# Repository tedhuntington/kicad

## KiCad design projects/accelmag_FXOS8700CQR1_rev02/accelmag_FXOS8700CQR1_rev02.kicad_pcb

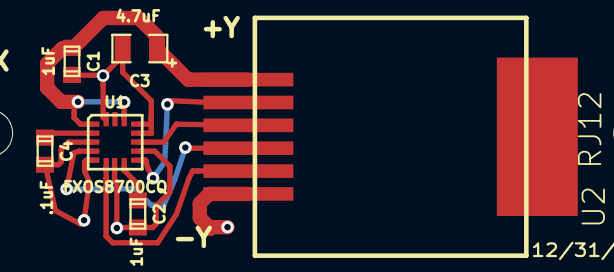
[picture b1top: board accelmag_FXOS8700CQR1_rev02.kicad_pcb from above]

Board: 2 copper layers, 8 parts (0 on the bottom side), 8 nets.

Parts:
C1, C2: 1uF; TED_SM0603_C
C3: 4.7uF; TED_SM2012_0805_ELEC_C
C4: .1uF; TED_SM0603_C
H1, H2: HOLE; TED_Hole_2_6mm
U1: FXOS8700CQ; TED_QFN16_3x5
U2: RJ12; TED_RJ12_855135002

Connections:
GND: C1.2, C2.2, C3.2, C4.2, U1.3, U1.5, U1.7, U1.10, U1.12, U1.13, U1.16, U2.1
INT1: U1.11, U2.4
INT2: U1.9, U2.5
unnamed: C2.1, U1.8
unnamed: C4.1, U1.2
SCL: U1.4, U2.3
SDA: U1.6, U2.2
Vdd: C1.1, C3.1, U1.1, U1.14, U2.6

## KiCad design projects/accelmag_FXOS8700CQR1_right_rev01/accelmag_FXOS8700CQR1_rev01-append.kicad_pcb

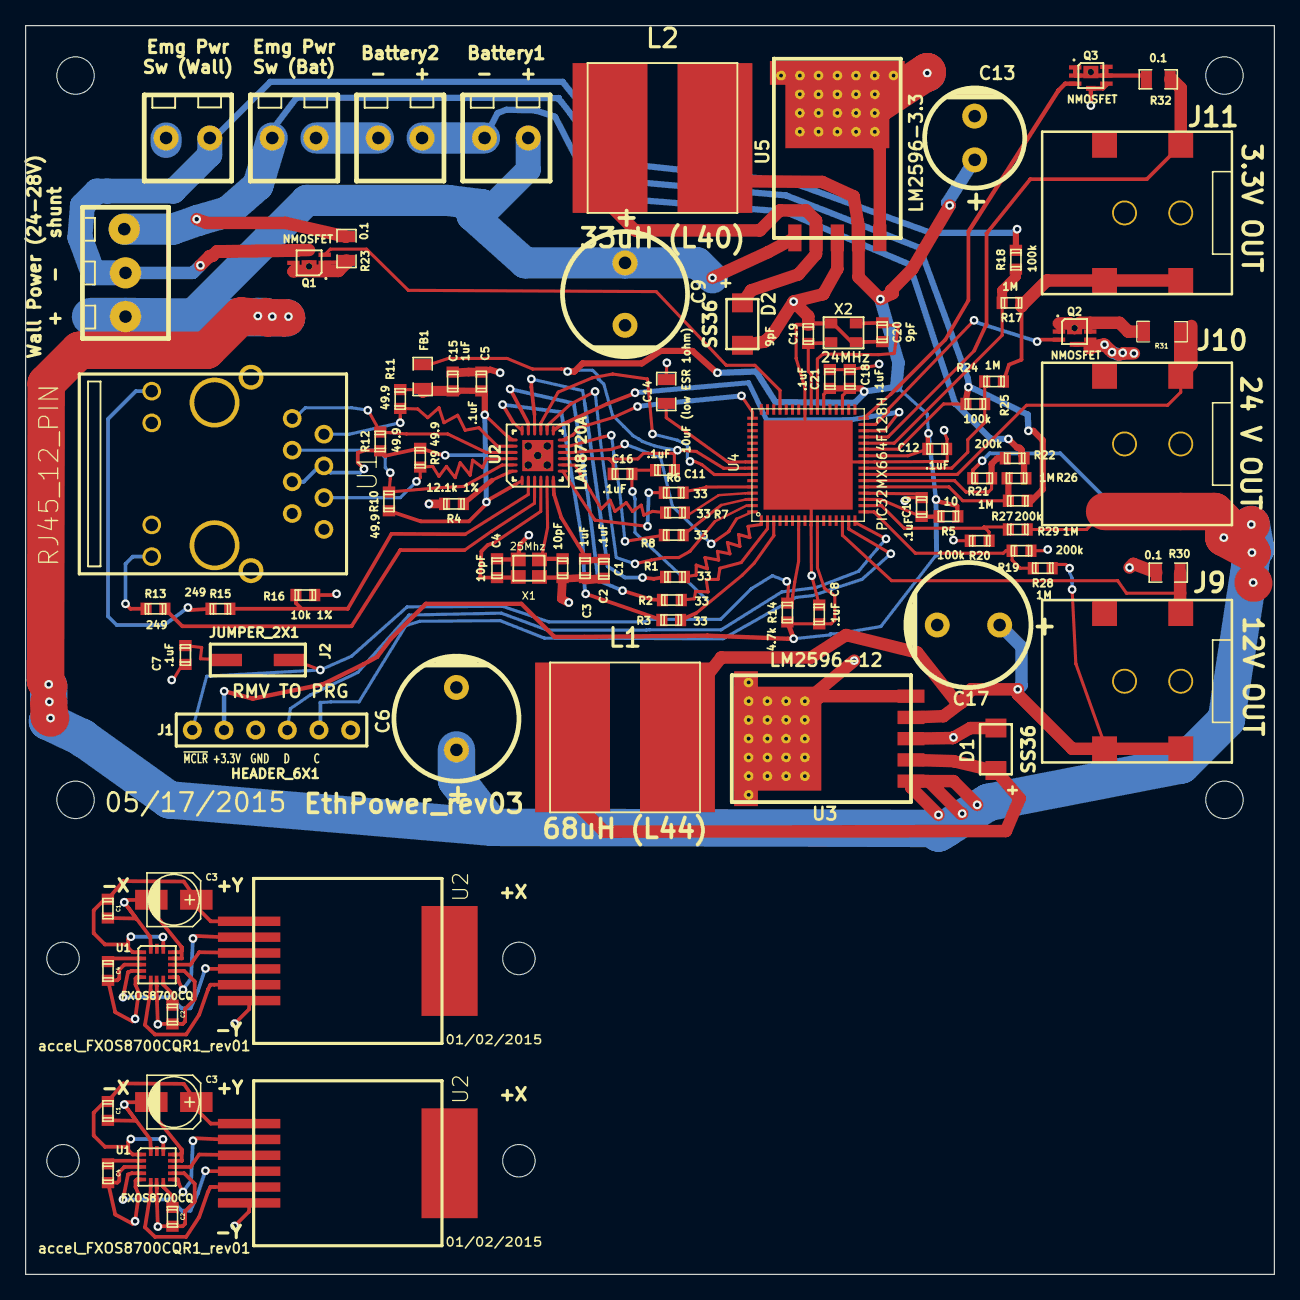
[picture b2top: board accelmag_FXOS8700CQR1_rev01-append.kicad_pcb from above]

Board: 2 copper layers, 100.0 x 100.0 mm, 98 parts (0 on the bottom side), 71 nets.

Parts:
C1, C1#3, C2, C2#3: 1uF; TED_SM0603
C1#2, C5, C7, C8, C10, C11, C12, C16, C18, C21: .1uF; TED_SM0603_C
C2#2, C15: 1uF; TED_SM0603_C
C3, C3#3: 4.7uF; TED_c_elec_4.3x4.3
C3#2, C4#2: 10pF; TED_SM0603_C
C4, C4#3: .1uF; TED_SM0603
C6, C9: 470uF; TED_c_elec_radial_10mm
C13: 680uF; TED_c_elec_radial_8mm
C14: 10uF (low ESR 1ohm); TED_SM0805_C
C17: 330uF; TED_c_elec_radial_10mm
C19, C20: 9pF; TED_SM0603_C
D1, D2: SS36; TED_DO-214AC
FB1: 500mA; TED_SM0805_R
H1, H1#3, H2, H2#3: HOLE; TED_Hole_2_6mm
H1#2, H2#2, H3, H4: HOLE; TED_Hole_3mm
J1: HEADER_6X1; TED_HEADER_6x1
J2: JUMPER_2X1; TED_HEADER_2x1_SMT
J3, J5, J6, J7: TERMINAL_2X1; TED_TERMINAL_3.5MM_2PIN
J8: TERMINAL_3X1; TED_TERMINAL_3.5MM_3PIN
J9, J10, J11: DC_2.1MM; TED_2.1mm_DC_SMD
L1: 68uH (L44); TED_INDUCTOR_12x12_SMD
L2: 33uH (L40); TED_INDUCTOR_12x12_SMD
Q1, Q2, Q3: NMOSFET; TED_PQFN6+1
R1, R2, R3, R6, R7, R8: 33; TED_SM0603_R
R4: 12.1k 1%; TED_SM0603_R
R5: 10; TED_SM0603_R
R9, R10, R11, R12: 49.9; TED_SM0603_R
R13, R15: 249; TED_SM0603_R
R14: 4.7k; TED_SM0603_R
R16: 10k 1%; TED_SM0603_R
R17, R19, R21, R24, R26, R28: 1M; TED_SM0603_R
R18, R20, R25: 100k; TED_SM0603_R
R22, R27, R29: 200k; TED_SM0603_R
R23, R30, R32: 0.1; TED_SM0805_R
R31: 0.1; TED_SM1206_R
U1, U1#3: FXOS8700CQ; TED_QFN16_3x5
U1#2: RJ45_12_PIN; TED_RJ45_12pin_Top
U2, U2#3: RJ12; TED_RJ12_855135002
U2#2: LAN8720A; TED_QFN24
U3: LM2596-12; TED_TO263
U4: PIC32MX664F128H; TED_QFN64+1
U5: LM2596-3.3; TED_TO263
X1: 25Mhz; TED_crystal_FA-20H
X2: 24MHz; TED_crystal_TSX3225

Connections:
3.3V: J11.1, R17.1, R24.1
12V: C17.1, J9.1, L1.2, R28.1, U3.4
AVDD: C5.1, C15.1, FB1.2, R9.1, R10.1, R11.1, R12.1, U1#2.4, U1#2.5, U2#2.1, U2#2.19
ECRSDV: R8.2, U4.62
EMDC: U2#2.13, U4.30
EMDIO: U2#2.12, U4.49
EREFCLK: U2#2.14, U4.63
ERXD0: R7.2, U4.61
ERXD1: R6.2, U4.60
ERXERR: U2#2.10, U4.64
ETXD0: R2.2, U4.2
ETXD1: R3.2, U4.3
ETXEN: R1.2, U4.1
GND: C1.2, C1#2.2, C1#3.2, C2.2, C2#2.2, C2#3.2, C3.2, C3#2.2, C3#3.2, C4.2, C4#2.1, C4#3.2, C5.2, C6.2, C7.2, C8.2, C9.2, C10.2, C11.2, C12.2, C13.2, C14.2, C15.2, C16.2, C17.2, C18.2, C19.2, C20.2, C21.2, D1.2, D2.2, J1.3, J5.1, Q2.2, Q3.2, R4.2, R16.2, R20.2, R29.2, R30.2, U1.3, U1.5, U1.7, U1.10, U1.12, U1.13, U1.16, U1#2.8, U1#2.10, U1#2.11, U1#3.3, U1#3.5, U1#3.7, U1#3.10, U1#3.12, U1#3.13, U1#3.16, U2.1, U2#2.25, U2#3.1, U3.3, U3.5, U4.9, U4.20, U4.25, U4.41, U4.65, U5.3, U5.5, X1.2, X1.4, X2.2, X2.4
GNDWALL: J5.2, J8.2, Q1.2, R18.2
GreenLED: R15.1, U1#2.9
INT1: U1.11, U1#3.11, U2.4, U2#3.4
INT2: U1.9, U1#3.9, U2.5, U2#3.5
unnamed: R15.2, R16.1, U2#2.2
unnamed: R13.2, U2#2.3
unnamed: C4.1, C4#3.1, U1.2, U1#3.2
unnamed: R4.1, U2#2.24
unnamed: C2.1, C2#3.1, U1.8, U1#3.8
unnamed: R7.1, U2#2.8
unnamed: R6.1, U2#2.7
unnamed: R8.1, U2#2.11
unnamed: R3.1, U2#2.18
unnamed: R2.1, U2#2.17
unnamed: R1.1, U2#2.16
unnamed: C4#2.2, U2#2.4, X1.3
unnamed: C3#2.1, U2#2.5, X1.1
unnamed: C10.1, R5.2, U4.19
unnamed: C19.1, U4.40, X2.1
unnamed: C7.1, J2.1
unnamed: C20.1, U4.39, X2.3
unnamed: C1#2.1, C2#2.1, U2#2.6
unnamed: Q1.3, R23.2
unnamed: J3.1, J6.2
unnamed: Q2.3, R31.2
unnamed: Q3.3, R32.2
unnamed: D1.1, L1.1, U3.2
unnamed: D2.1, L2.1, U5.2
PGEC1_RB1: J1.5, U4.15
PGED1_RB0: J1.4, U4.16
RXN: R9.2, U1#2.6, U2#2.22
RXP: R10.2, U1#2.3, U2#2.23
SCL: U1.4, U1#3.4, U2.3, U2#3.3
SDA: U1.6, U1#3.6, U2.2, U2#3.2
SenseBatteryConnected: R24.2, R25.1, U4.24
SenseCurrent3.3v: J11.2, R32.1, U4.29
SenseCurrent12v: J9.2, R30.1, U4.14
SenseCurrent24v: J10.2, R31.1, U4.23
SenseCurrentCharger/GNDBATTERY: J6.1, J8.3, R23.1, R25.2, R27.2, U4.27
SenseVolt12VOut: R28.2, R29.1, U4.17
SenseVoltBattery1: R21.2, R22.1, U4.22
SenseVoltBattery2: R26.2, R27.1, U4.21
SenseVoltFull: R19.2, R20.1, U4.18
SenseWallConnected: R17.2, R18.1, U4.28
Switch3.3V: Q3.1, U4.32
Switch24V: Q2.1, U4.31
SwitchCharger: Q1.1, U4.45
TXN: R11.2, U1#2.2, U2#2.20
TXP: R12.2, U1#2.1, U2#2.21
VBat2: J3.2, J7.1, R22.2, R26.1
VCAP: C14.1, U4.56
VDD: C8.1, C11.1, C12.1, C13.1, C16.1, C18.1, C21.1, FB1.1, J1.2, L2.2, R5.1, R14.1, U2#2.9, U4.10, U4.26, U4.35, U4.38, U4.57, U5.4
VWallVBat: C6.1, C9.1, J7.2, J8.1, J10.1, R19.1, R21.1, U3.1, U5.1
Vdd: C1.1, C1#3.1, C3.1, C3#3.1, U1.1, U1.14, U1#3.1, U1#3.14, U2.6, U2#3.6
YellowLED: R13.1, U1#2.12
nRST: U2#2.15, U4.58
~MCLR~: J1.1, J2.2, R14.2, U4.7
